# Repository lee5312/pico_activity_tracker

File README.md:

# pico_activity_tracker
ECE 362 Final Project 

## Usage
Note: You will have to edit or remove the first 4 lines of platformio.ini for it to compile. Removing it should generally be fine.

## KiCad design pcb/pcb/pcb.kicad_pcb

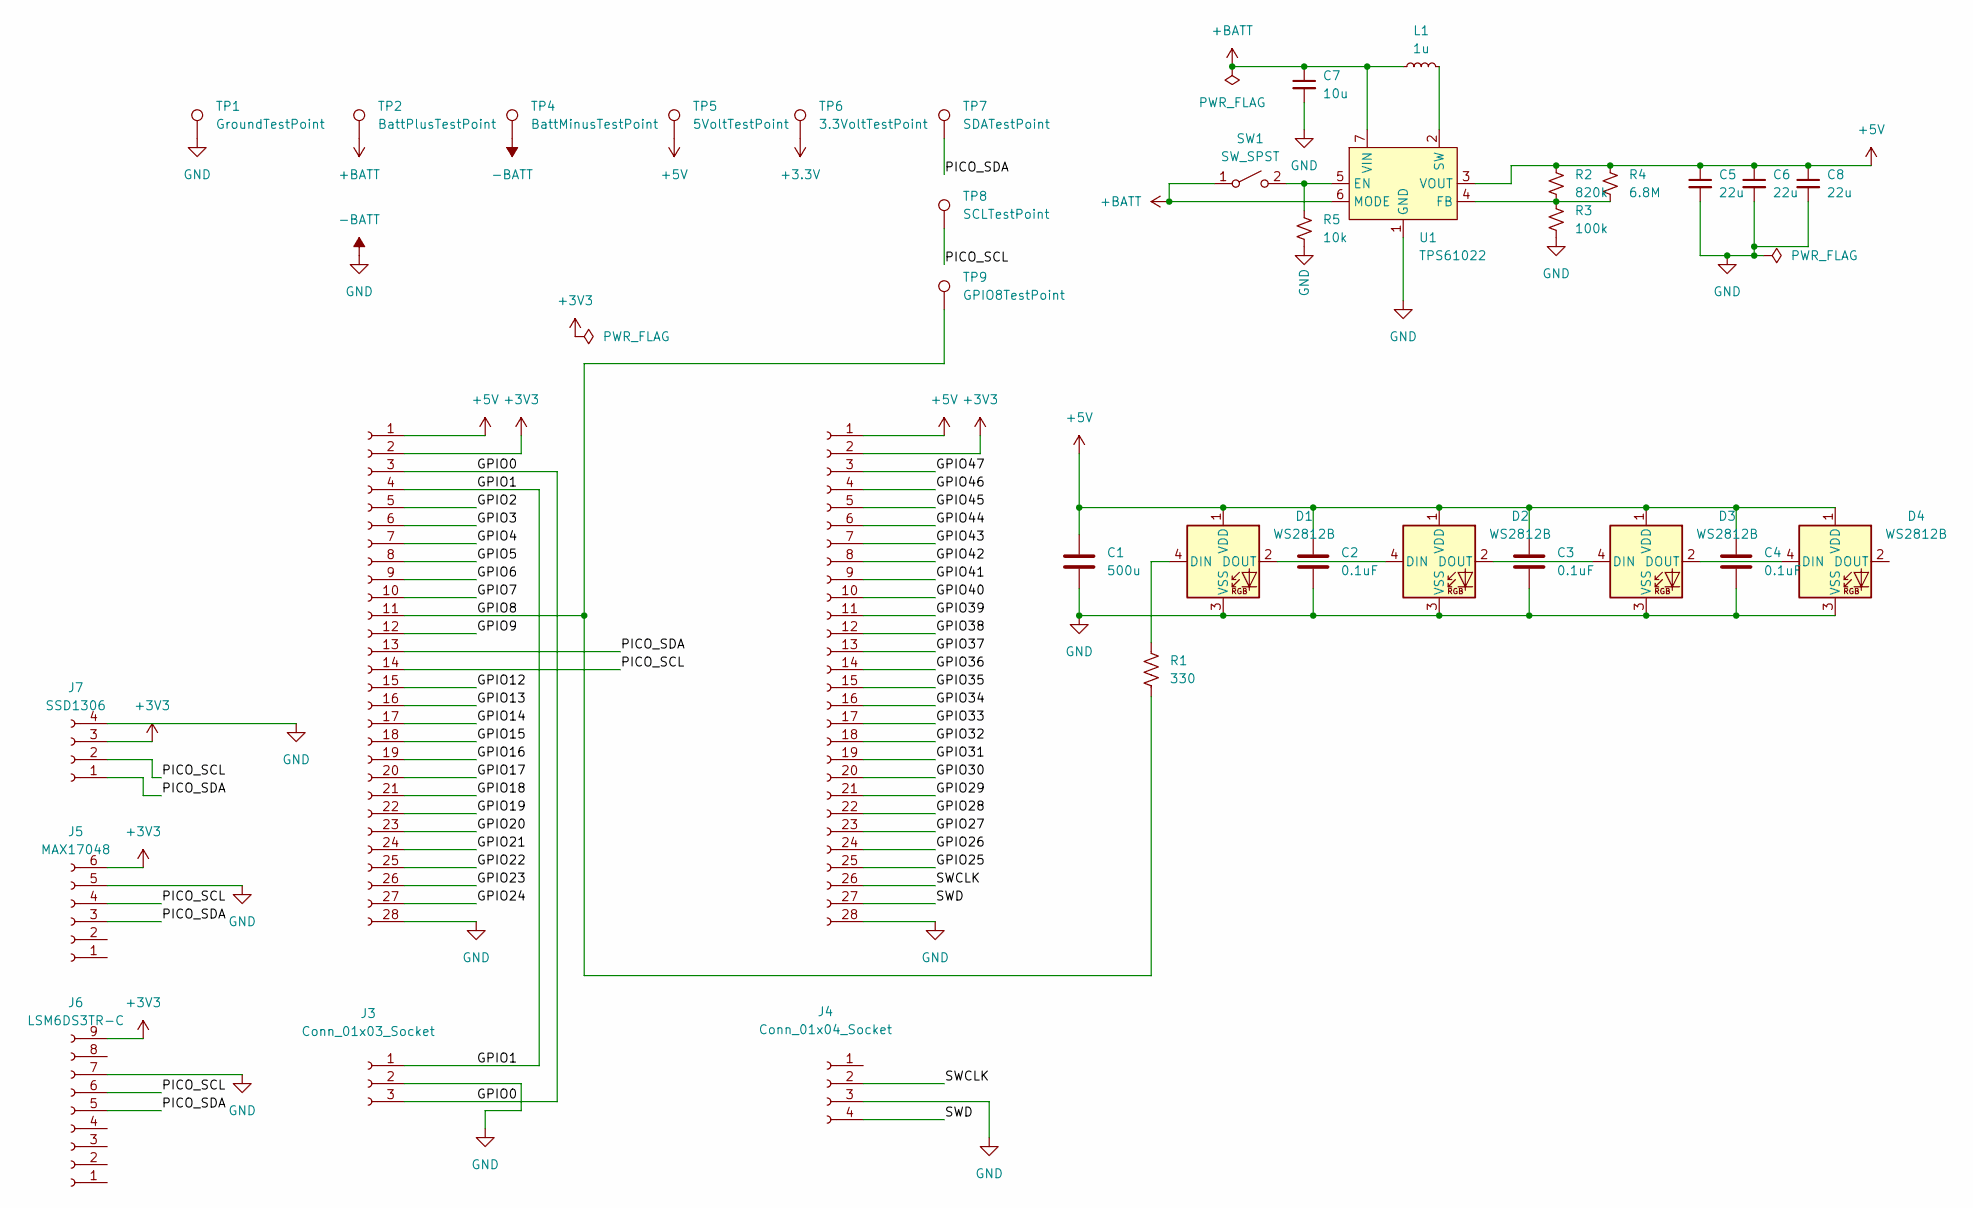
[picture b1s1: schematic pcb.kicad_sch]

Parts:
C1: 500u; C_0805_2012Metric_Pad1.18x1.45mm_HandSolder
C2, C3, C4: 0.1uF; C_0805_2012Metric_Pad1.18x1.45mm_HandSolder
C5, C6, C8: 22u; C_0805_2012Metric_Pad1.18x1.45mm_HandSolder
C7: 10u; C_0805_2012Metric_Pad1.18x1.45mm_HandSolder
D1, D2, D3, D4: WS2812B; LED_WS2812B_PLCC4_5.0x5.0mm_P3.2mm
J1, J2: Conn_01x28_Socket; PinSocket_1x28_P2.54mm_Vertical
J3: Conn_01x03_Socket; PinSocket_1x03_P2.54mm_Vertical
J4: Conn_01x04_Socket; PinSocket_1x04_P2.54mm_Vertical
J5: MAX17048; PinSocket_1x06_P2.54mm_Vertical
J6: LSM6DS3TR-C; PinSocket_1x09_P2.54mm_Vertical
J7: SSD1306; PinSocket_1x04_P2.54mm_Vertical
L1: 1u; L_0805_2012Metric_Pad1.05x1.20mm_HandSolder
R1: 330; R_0805_2012Metric_Pad1.20x1.40mm_HandSolder
R2: 820k; R_0805_2012Metric_Pad1.20x1.40mm_HandSolder
R3: 100k; R_0805_2012Metric_Pad1.20x1.40mm_HandSolder
R4: 6.8M; R_0805_2012Metric_Pad1.20x1.40mm_HandSolder
R5: 10k; R_0805_2012Metric_Pad1.20x1.40mm_HandSolder
SW1: SW_SPST; SW_DIP_SPSTx01_Slide_6.7x4.1mm_W6.73mm_P2.54mm_LowProfile_J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
TP1: GroundTestPoint; TestPoint_Pad_D1.5mm
TP2: BattPlusTestPoint; TestPoint_Pad_D1.5mm
TP4: BattMinusTestPoint; TestPoint_Pad_D1.5mm
TP5: 5VoltTestPoint; TestPoint_Pad_D1.5mm
TP6: 3.3VoltTestPoint; TestPoint_Pad_D1.5mm
TP7: SDATestPoint; TestPoint_Pad_D1.5mm
TP8: SCLTestPoint; TestPoint_Pad_D1.5mm
TP9: GPIO8TestPoint; TestPoint_Pad_D1.5mm
U1: TPS61022; Texas_RWU0007A_VQFN-7_2x2mm_P0.5mm

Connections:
+3.3V: TP6.1
+3V3: J1.2, J2.2, J5.6, J6.9, J7.3
+5V: C1.1, C2.1, C3.1, C4.1, C5.1, C6.1, C8.1, D1.1 (VDD), D2.1 (VDD), D3.1 (VDD), D4.1 (VDD), J1.1, J2.1, R2.1, R4.1, TP5.1, U1.3 (VOUT)
+BATT: C7.1, L1.1, SW1.1 (A), TP2.1, U1.6 (MODE), U1.7 (VIN)
-BATT: C1.2, C2.2, C3.2, C4.2, C5.2, C6.2, C7.2, C8.2, D1.3 (VSS), D2.3 (VSS), D3.3 (VSS), D4.3 (VSS), J1.28, J2.28, J3.2, J4.3, J5.5, J6.7, J7.4, R3.2, R5.2, TP1.1, TP4.1, U1.1 (GND)
/GPIO0: J1.3, J3.3
/GPIO1: J1.4, J3.1
/GPIO2: J1.5
/GPIO3: J1.6
/GPIO4: J1.7
/GPIO5: J1.8
/GPIO6: J1.9
/GPIO7: J1.10
/GPIO8: J1.11, R1.1, TP9.1
/GPIO9: J1.12
/GPIO12: J1.15
/GPIO13: J1.16
/GPIO14: J1.17
/GPIO15: J1.18
/GPIO16: J1.19
/GPIO17: J1.20
/GPIO18: J1.21
/GPIO19: J1.22
/GPIO20: J1.23
/GPIO21: J1.24
/GPIO22: J1.25
/GPIO23: J1.26
/GPIO24: J1.27
/GPIO25: J2.25
/GPIO26: J2.24
/GPIO27: J2.23
/GPIO28: J2.22
/GPIO29: J2.21
/GPIO30: J2.20
/GPIO31: J2.19
/GPIO32: J2.18
/GPIO33: J2.17
/GPIO34: J2.16
/GPIO35: J2.15
/GPIO36: J2.14
/GPIO37: J2.13
/GPIO38: J2.12
/GPIO39: J2.11
/GPIO40: J2.10
/GPIO41: J2.9
/GPIO42: J2.8
/GPIO43: J2.7
/GPIO44: J2.6
/GPIO45: J2.5
/GPIO46: J2.4
/GPIO47: J2.3
/PICO_SCL: J1.14, J5.4, J6.6, J7.2, TP8.1
/PICO_SDA: J1.13, J5.3, J6.5, J7.1, TP7.1
/SWCLK: J2.26, J4.2
/SWD: J2.27, J4.4
unnamed: D1.4 (DIN), R1.2
unnamed: D1.2 (DOUT), D2.4 (DIN)
unnamed: D2.2 (DOUT), D3.4 (DIN)
unnamed: D3.2 (DOUT), D4.4 (DIN)
unnamed: R5.1, SW1.2 (B), U1.5 (EN)
unnamed: R2.2, R3.1, R4.2, U1.4 (FB)
unnamed: L1.2, U1.2 (SW)

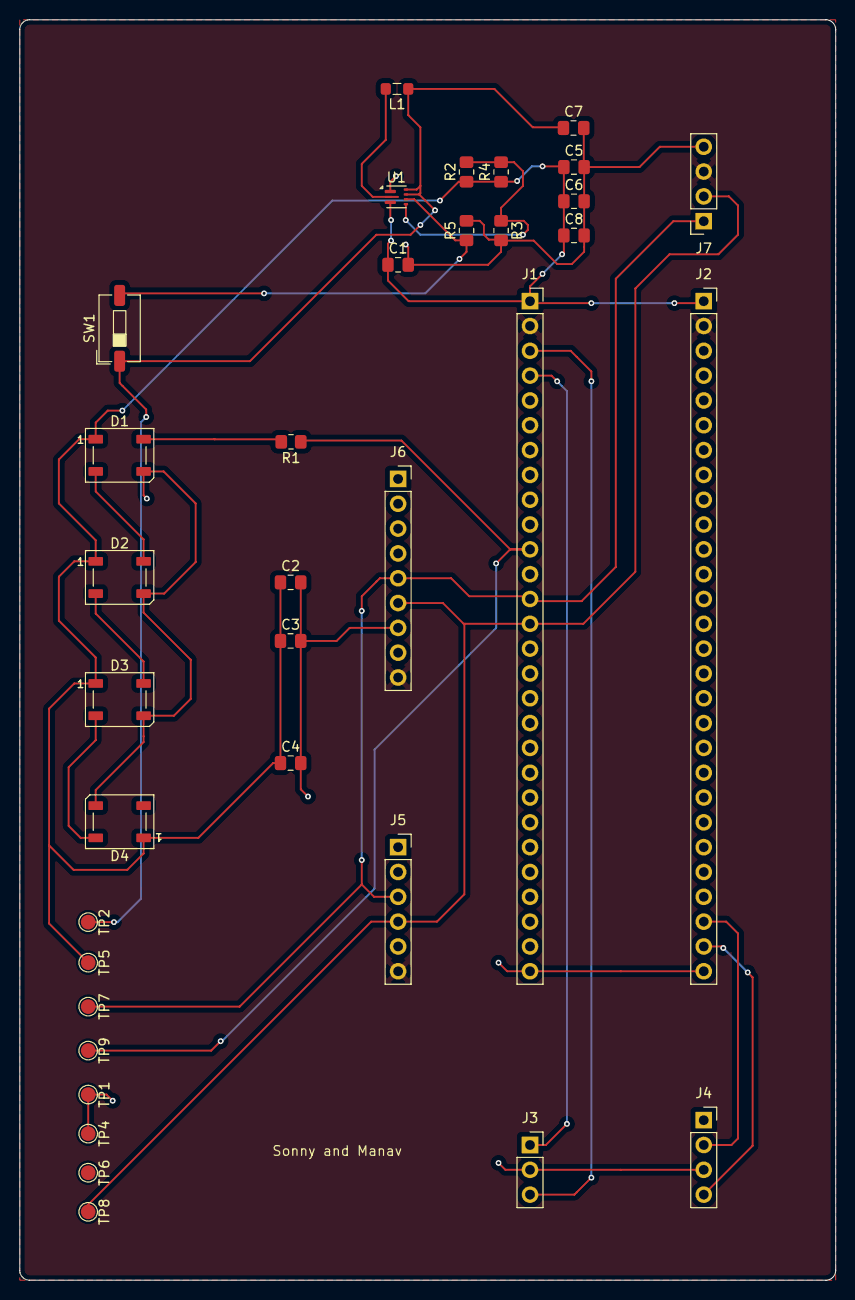
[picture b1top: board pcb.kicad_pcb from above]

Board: 2 copper layers, 83.5 x 129.0 mm, 35 parts (0 on the bottom side), 18 nets.

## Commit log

2025-10-24 feat: add VSCode config to gitignore and update README with build instructions
    - Ignore VSCode C++ configuration and launch files
    - Add usage section with platformio.ini compilation note
2025-11-07 initial commit pcb
2025-11-07 gitattributes
2025-11-07 [wip] battery management
2025-11-18 hopefully done w/ schmematic
2025-11-19 pcb layout, calorie model
2025-11-19 completed pcb
2025-11-19 deleted old files, fixed 3v3
2025-11-19 add test points 2
2025-11-19 finished pcb
2025-11-19 draft
2025-11-27 imu_dae_version1
2025-11-30 Add ring-buffer-based step detection for IMU
2025-12-01 works well but tunning needed for step output
2025-12-01 Almost final version except for ringbuffer tuning
